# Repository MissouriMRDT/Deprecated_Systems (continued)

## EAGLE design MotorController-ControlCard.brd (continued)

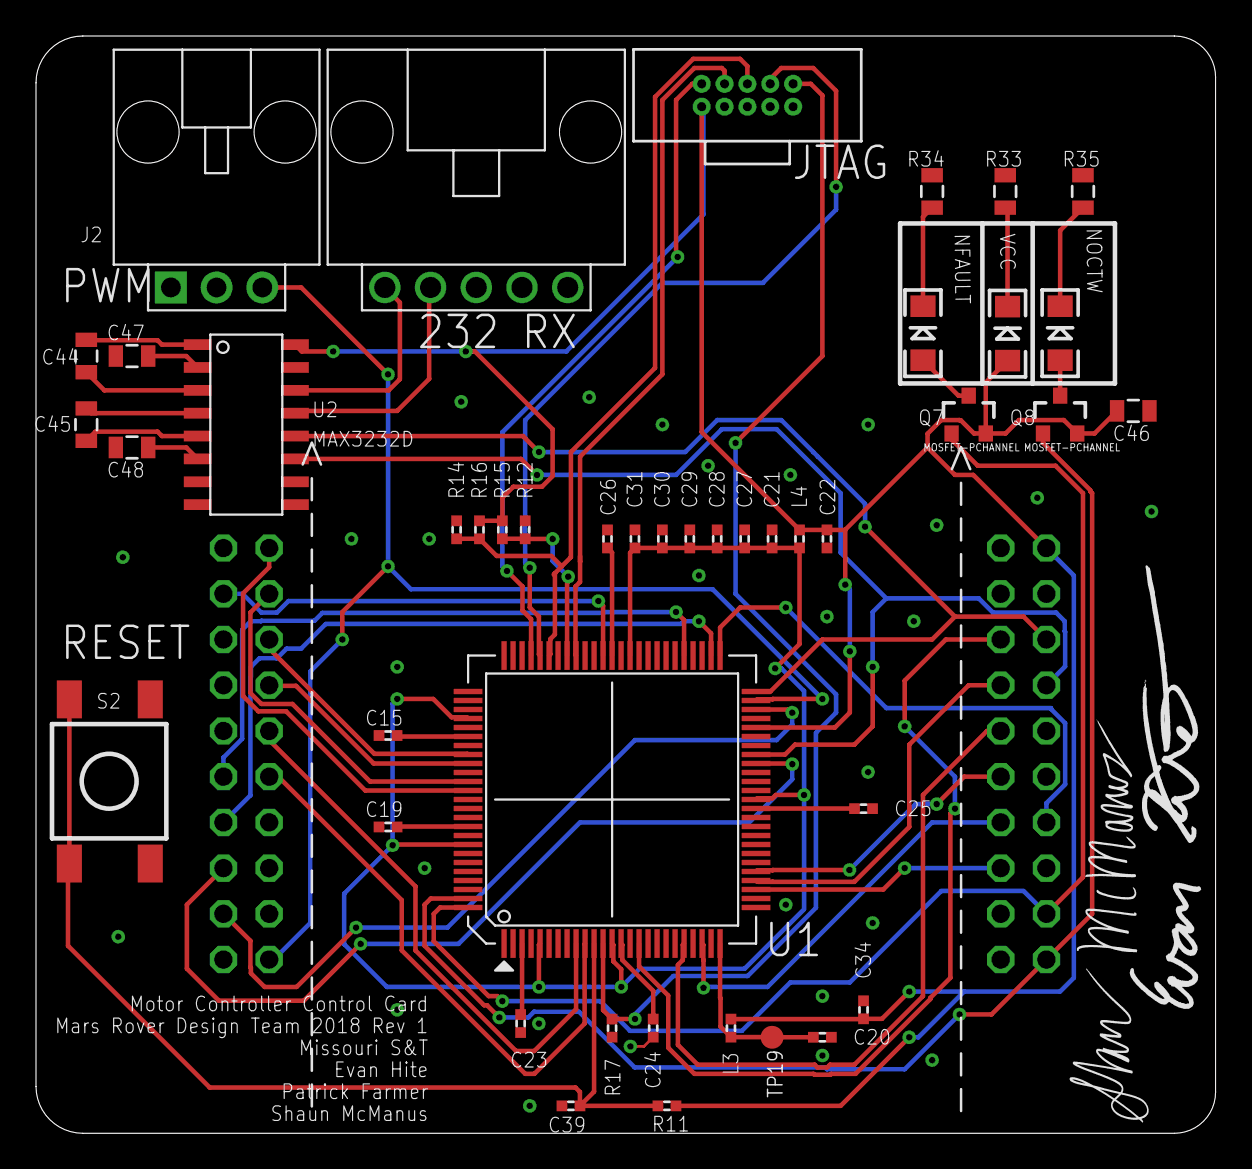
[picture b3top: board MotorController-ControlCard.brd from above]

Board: 2 copper layers, 65.5 x 61.0 mm, 47 parts (1 on the bottom side), 53 nets.

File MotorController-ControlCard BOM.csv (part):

Partlist exported from C:/Users/shotp/Documents/GitHub/MotorController-ControlCard/MotorController-ControlCard.sch at 1/24/2018 7:32 PM

Part Value                     Device                    Package                        Description                      OPERATING_VOLTAGE ORIENT PARTNO     PROD_ID     TP_SIGNAL_NAME
"C15  2.2u                      C-USC0402                 C0402                          CAPACITOR, American symbol                                                                     "
"C19  2.2u                      C-USC0402                 C0402                          CAPACITOR, American symbol                                                                     "
"C20  2.2u                      C-USC0402                 C0402                          CAPACITOR, American symbol                                                                     "
"C21  2.2u                      C-USC0402                 C0402                          CAPACITOR, American symbol                                                                     "
"C22  2.2u                      C-USC0402                 C0402                          CAPACITOR, American symbol                                                                     "
"C23  2.2u                      C-USC0402                 C0402                          CAPACITOR, American symbol                                                                     "
"C24  2.2u                      C-USC0402                 C0402                          CAPACITOR, American symbol                                                                     "
"C25  2.2u                      C-USC0402                 C0402                          CAPACITOR, American symbol                                                                     "
"C26  2.2u                      C-USC0402                 C0402                          CAPACITOR, American symbol                                                                     "
"C27  2.2u                      C-USC0402                 C0402                          CAPACITOR, American symbol                                                                     "
"C28  2.2u                      C-USC0402                 C0402                          CAPACITOR, American symbol                                                                     "
"C29  2.2u                      C-USC0402                 C0402                          CAPACITOR, American symbol                                                                     "
"C30  2.2u                      C-USC0402                 C0402                          CAPACITOR, American symbol                                                                     "
"C31  2.2u                      C-USC0402                 C0402                          CAPACITOR, American symbol                                                                     "
"C34  0.1u                      C-USC0402                 C0402                          CAPACITOR, American symbol                                                                     "
"C39  0.1u                      C-USC0402                 C0402                          CAPACITOR, American symbol                                                                     "
C44  0.1u                      CAP0805                   0805                           Capacitor                                                                                      
C45  0.1u                      CAP0805                   0805                           Capacitor                                                                                      
C46  0.1u                      CAP0805                   0805                           Capacitor                                                                                      
C47  0.1u                      CAP0805                   0805                           Capacitor                                                                                      
C48  0.1u                      CAP0805                   0805                           Capacitor                                                                                      
D7                             LED1206                   LED-1206                       LEDs                                                                                           
D8                             LED1206                   LED-1206                       LEDs                                                                                           
D9                             LED1206                   LED-1206                       LEDs                                                                                           
J2   SL03THROUGH_HOLE          SL03THROUGH_HOLE          MOLEX_SL_03_TH                 Molex 3-pin SL connector                           HORIZ  0705550002                           
"L3   BKP1005HS221-T            L-US0402                  R0402                          INDUCTOR, American symbol                                                                      "
"L4   BLM15PD600SN1D            L-US0402                  R0402                          INDUCTOR, American symbol                                                                      "
Q7   MOSFET-PCHANNEL           MOSFET-PCHANNEL           SOT23-3                        Generic PMOSFET                                                      TRANS-08285               
Q8   MOSFET-PCHANNEL           MOSFET-PCHANNEL           SOT23-3                        Generic PMOSFET                                                      TRANS-08285               
"R11  2.2k                      R-US_R0402                R0402                          RESISTOR, American symbol                                                                      "
"R12  2.2k                      R-US_R0402                R0402                          RESISTOR, American symbol                                                                      "
"R14  2.2k                      R-US_R0402                R0402                          RESISTOR, American symbol                                                                      "
"R15  820                       R-US_R0402                R0402                          RESISTOR, American symbol                                                                      "
"R16  820                       R-US_R0402                R0402                          RESISTOR, American symbol                                                                      "
"R17  2.2k                      R-US_R0402                R0402                          RESISTOR, American symbol                                                                      "
R33  330                       RESISTOR0805-RES          0805                           Resistor                                                                                       
R34  330                       RESISTOR0805-RES          0805                           Resistor                                                                                       
R35  330                       RESISTOR0805-RES          0805                           Resistor                                                                                       
S2   TP-1138K9-BE1125          FSMJSMA                   FSMJSMA                                                                                                                       
"TP19 TESTPAD_TPB1,27           TESTPAD_TPB1,27           TESTPAD_B1,27                  Test pad                                                                                       "
U$1  TIVA-123                  TIVA-123                  TIVA-C                         TIVA-C DEV BOARD (NON-CONNECTED)                                                               
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
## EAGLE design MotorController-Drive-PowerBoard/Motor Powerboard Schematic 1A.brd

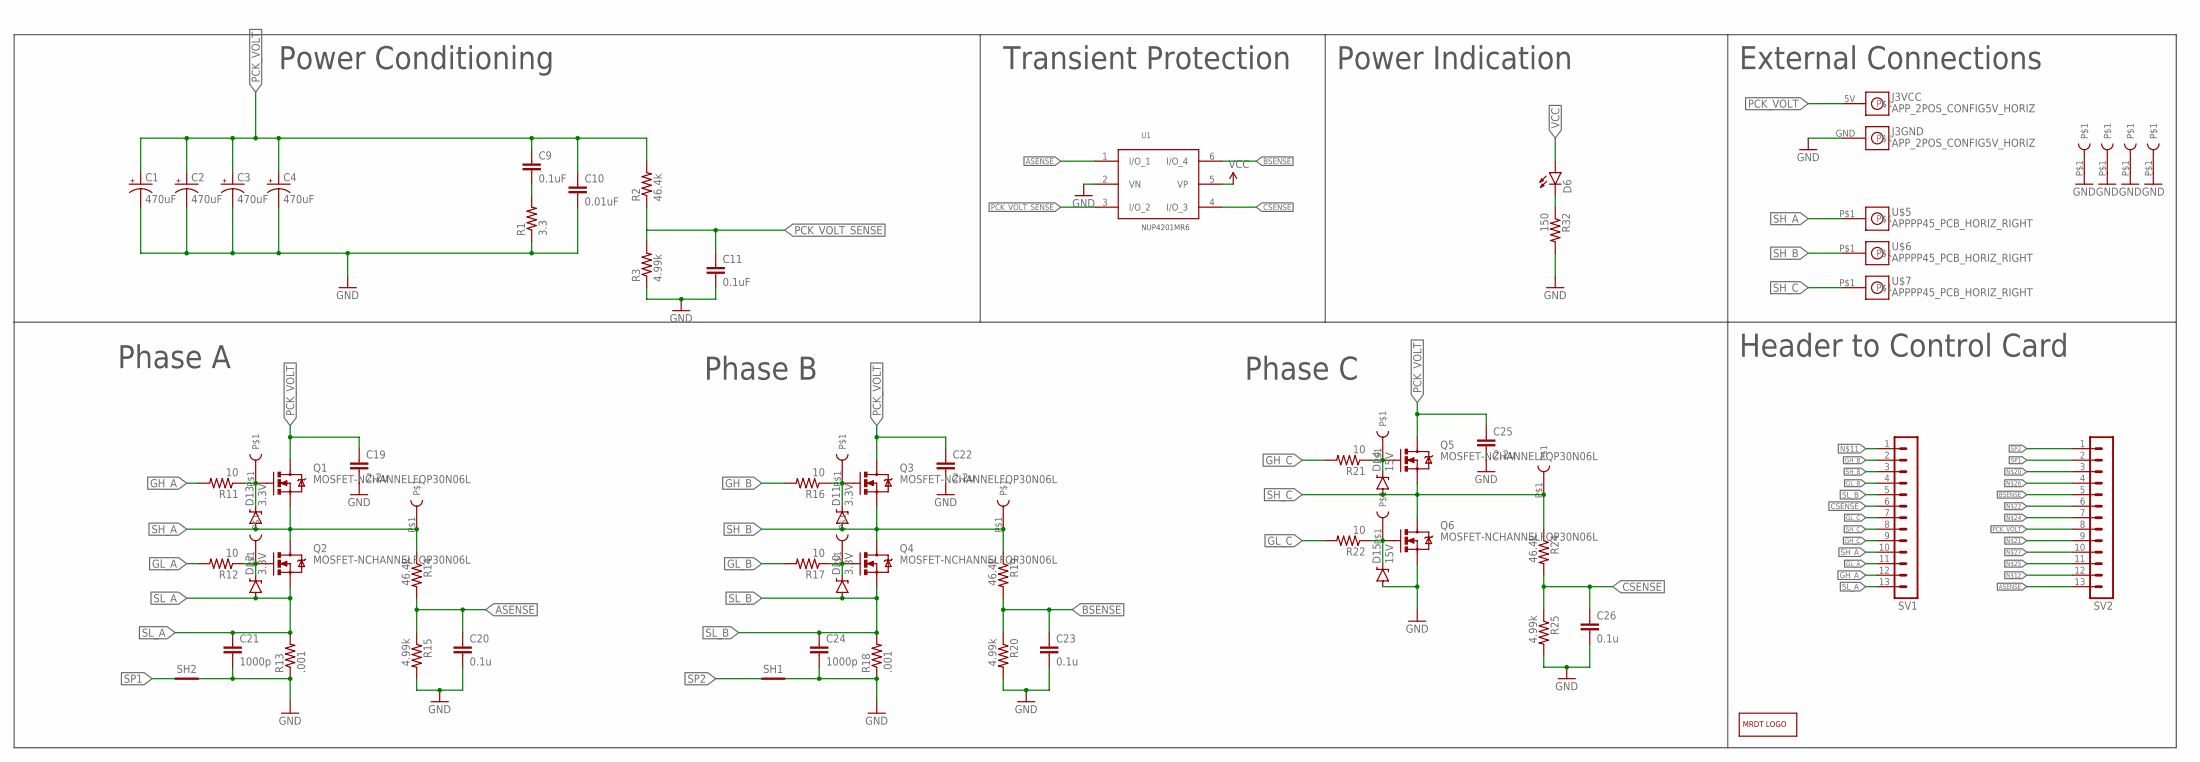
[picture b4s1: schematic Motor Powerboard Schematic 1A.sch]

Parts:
C1, C2, C3, C4: 470uF; CPOL-RADIAL-1000UF-25V
C9, C11: 0.1uF; 0805
C10: 0.01uF; 0805
C19, C22, C25: 2.2u; 1206
C20, C23, C26: 0.1u; 0805
C21, C24: 1000p; 0805
D6: LED1206; LED-1206
D10, D11, D12, D13: 3.3V; SOD-323
D14, D15: 15V; SOD-323
J3: APP_2POS_CONFIG5V_HORIZ; APP45_5V_HORIZ_CONFIG
LOGO1: MRDT_LOGO
Q1, Q2, Q3, Q4, Q5, Q6: MOSFET-NCHANNELFQP30N06L; TO220V
R1: 3.3; 1206
R2, R14, R19, R24: 46.4k; 0805
R3, R15, R20, R25: 4.99k; 0805
R11, R12, R16, R17, R21, R22: 10; 0805
R13, R18: .001; 1206
R32: 150; 0805
SH1, SH2: SHORT-HT5; SHORT_TOP-50
SV1, SV2: MA13-1
U1: NUP4201MR6; TSOP-6
U$5, U$6, U$7: APPPP45_PCB_HORIZ_RIGHT; APP45_PCB_HORIZ_RIGHT
U$12, U$15, U$16, U$17, U$18, U$19, U$20, U$24, U$25, U$26, U$27, U$28, U$29: TEST_POINT_0.1INDIAM

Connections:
ASENSE: C20.1, R14.2, R15.1, SV2.13, U1.1 (I/O_1)
BSENSE: C23.1, R19.2, R20.1, SV2.5, U1.6 (I/O_4)
CSENSE: C26.1, R24.2, R25.1, SV1.6, U1.4 (I/O_3)
GH_A: R11.2, SV1.12
GH_B: R16.2, SV1.2
GH_C: R21.2, SV1.9
GL_A: R12.2, SV1.11
GL_B: R17.2, SV1.4
GL_C: R22.2, SV1.7
GND: C1.2 (-), C2.2 (-), C3.2 (-), C4.2 (-), C10.2, C11.2, C19.2, C20.2, C21.2, C22.2, C23.2, C24.2, C25.2, C26.2, D15.A, J3.GND, Q6.3 (S), R1.1, R3.1, R13.1, R15.2, R18.1, R20.2, R25.2, R32.2, SH1.2, SH2.2, U1.2 (VN), U$26.P$1, U$27.P$1, U$28.P$1, U$29.P$1
unnamed: C9.2, R1.2
unnamed: D13.C, Q1.1 (G), R11.1, U$12.P$1
unnamed: D11.C, Q3.1 (G), R16.1, U$16.P$1
unnamed: D10.C, Q4.1 (G), R17.1, U$17.P$1
unnamed: D12.C, Q2.1 (G), R12.1, U$15.P$1
unnamed: D14.C, Q5.1 (G), R21.1, U$18.P$1
unnamed: D15.C, Q6.1 (G), R22.1, U$19.P$1
unnamed: D6.C, R32.1
PCK_VOLT: C1.1 (+), C2.1 (+), C3.1 (+), C4.1 (+), C9.1, C10.1, C19.1, C22.1, C25.1, J3.5V, Q1.2 (D), Q3.2 (D), Q5.2 (D), R2.2, SV2.8
PCK_VOLT_SENSE: C11.1, R2.1, R3.2, U1.3 (I/O_2)
SH_A: D13.A, Q1.3 (S), Q2.2 (D), R14.1, SV1.10, U$5.P$1, U$25.P$1
SH_B: D11.A, Q3.3 (S), Q4.2 (D), R19.1, SV1.3, U$6.P$1, U$24.P$1
SH_C: D14.A, Q5.3 (S), Q6.2 (D), R24.1, SV1.8, U$7.P$1, U$20.P$1
SL_A: C21.1, D12.A, Q2.3 (S), R13.2, SV1.13
SL_B: C24.1, D10.A, Q4.3 (S), R18.2, SV1.5
SP1: SH2.1, SV2.2
SP2: SH1.1, SV2.1
VCC: D6.A, U1.5 (VP)

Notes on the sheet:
Transient Protection
Phase A
Phase B
Phase C
External Connections
Power Indication
Power Conditioning
Header to Control Card

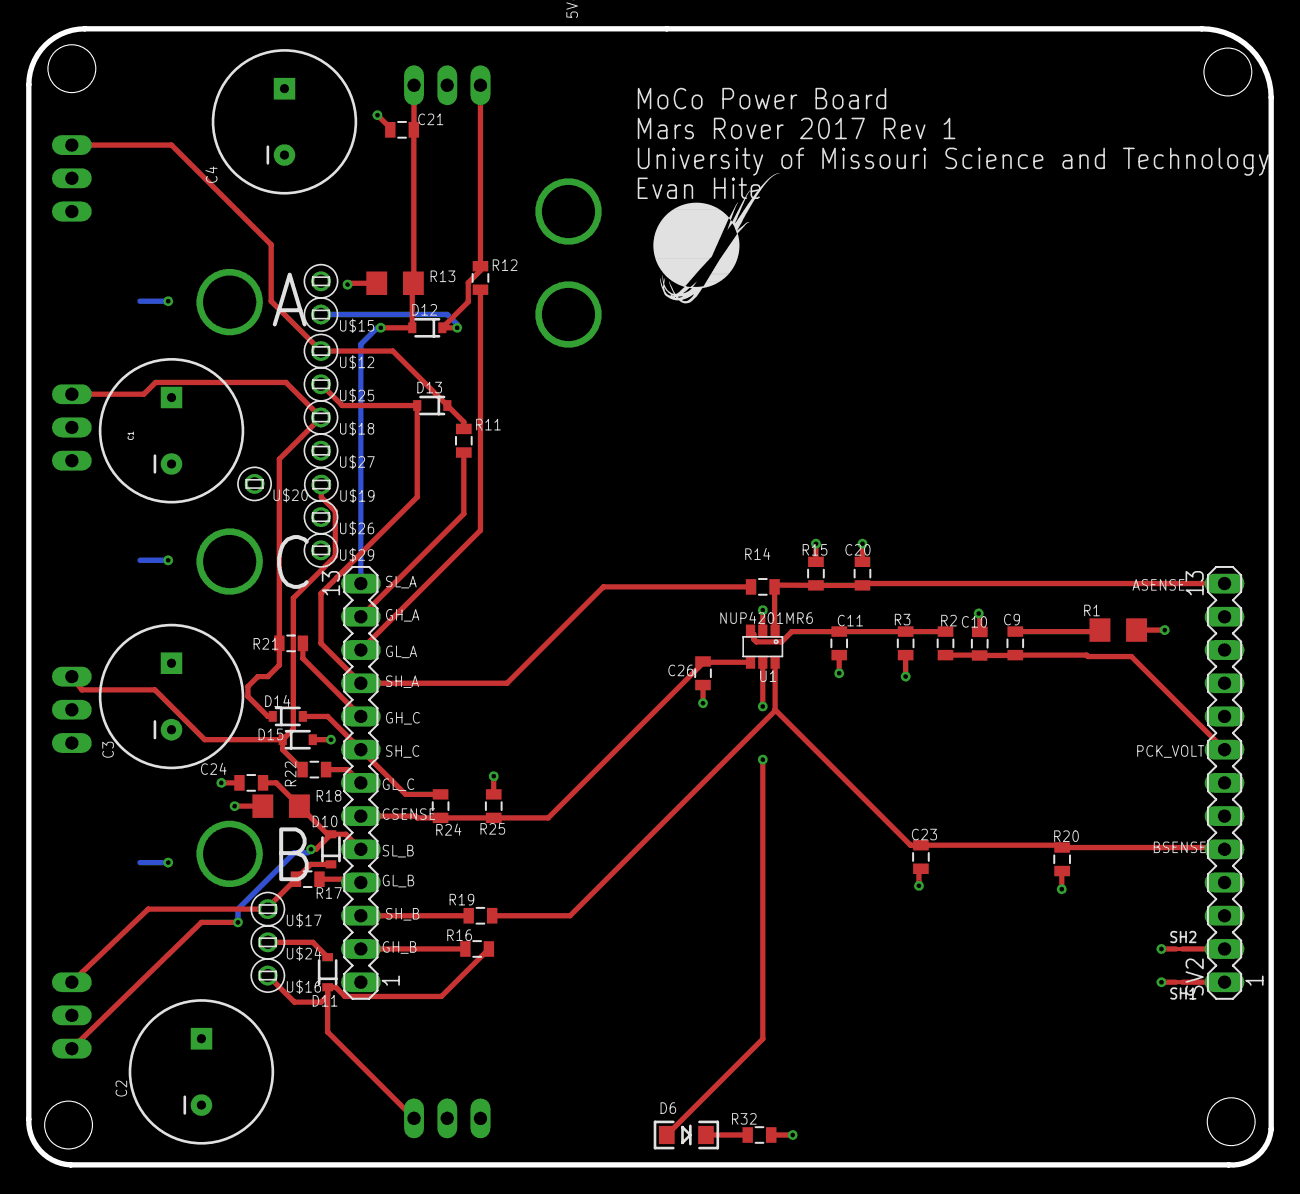
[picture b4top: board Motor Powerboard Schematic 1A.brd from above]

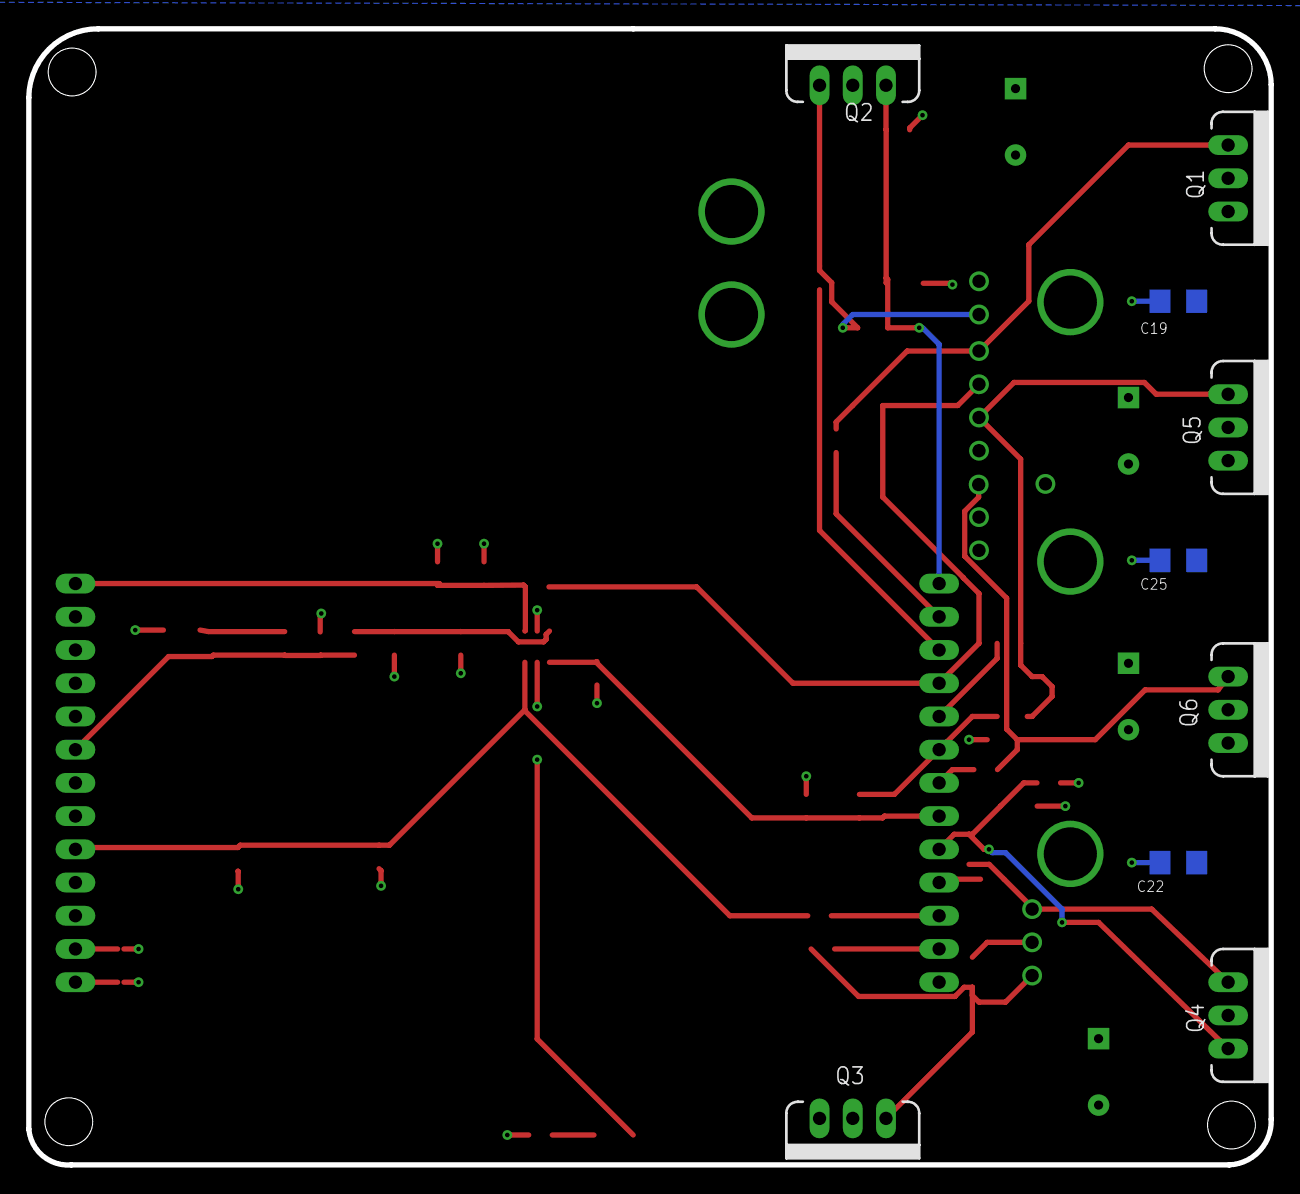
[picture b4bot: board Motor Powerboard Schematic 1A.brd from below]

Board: 4 copper layers, 95.0 x 86.9 mm, 69 parts (9 on the bottom side), 28 nets.

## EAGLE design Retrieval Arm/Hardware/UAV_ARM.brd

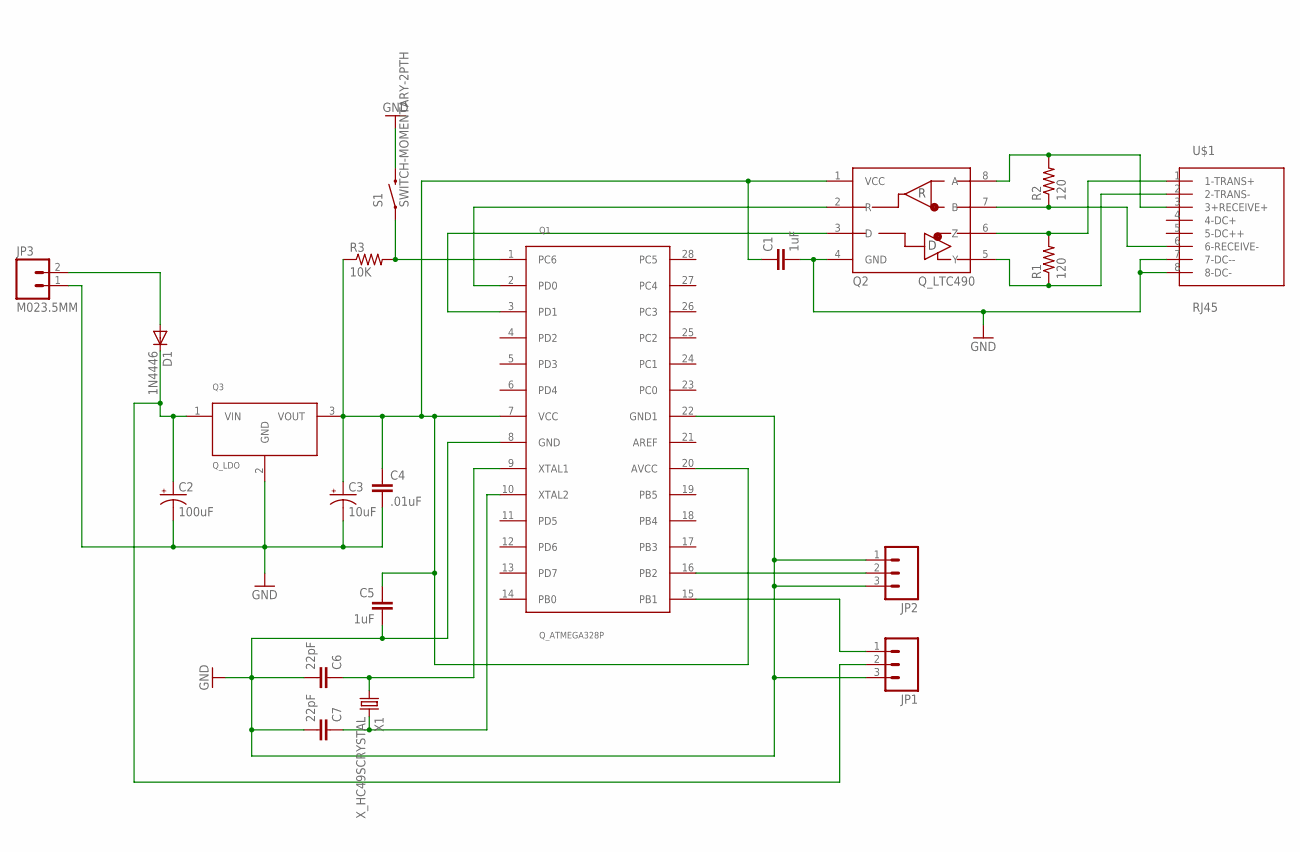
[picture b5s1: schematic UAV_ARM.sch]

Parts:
C1, C5: 1uF; CAP-PTH-SMALL-KIT
C2: 100uF; CPOL-RADIAL-100UF-25V
C3: 10uF; CPOL-RADIAL-10UF-25V
C4: .01uF; CAP-PTH-SMALL-KIT
C6, C7: 22pF; CAP-PTH-SMALL-KIT
D1: 1N4446; DO35-10
JP1, JP2: M03POLAR; MOLEX-1X3
JP3: M023.5MM; SCREWTERMINAL-3.5MM-2
Q1: Q_ATMEGA328P; DIP28
Q2: Q_LTC490; DIP8
Q3: Q_LDO; TO-220
R1, R2: 120; 0204/7
R3: 10K; 0204/7
S1: SWITCH-MOMENTARY-2PTH; TACTILE-PTH
U$1: RJ45; RJ45-CAT5E
X1: X_HC49SCRYSTAL; HC-49

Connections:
GND: C1.2, C2.2 (-), C3.2 (-), C4.2, C5.2, C6.2, C7.2, JP1.3, JP2.1, JP2.3, JP3.1, Q1.8 (GND), Q1.22 (GND1), Q2.4 (GND), Q3.2 (GND), S1.3 (2), U$1.7 (7-DC--), U$1.8 (8-DC-)
unnamed: Q2.8 (A), R2.2, U$1.3 (3+RECEIVE+)
unnamed: Q2.7 (B), R2.1, U$1.6 (6-RECEIVE-)
unnamed: Q2.5 (Y), R1.1, U$1.2 (2-TRANS-)
unnamed: Q2.6 (Z), R1.2, U$1.1 (1-TRANS+)
unnamed: C2.1 (+), D1.C, JP1.2, Q3.1 (VIN)
unnamed: C1.1, C3.1 (+), C4.1, C5.1, Q1.7 (VCC), Q1.20 (AVCC), Q2.1 (VCC), Q3.3 (VOUT), R3.1
unnamed: Q1.3 (PD1), Q2.3 (D)
unnamed: Q1.2 (PD0), Q2.2 (R)
unnamed: Q1.1 (PC6), R3.2, S1.1
unnamed: C6.1, Q1.9 (XTAL1), X1.P$1 (1)
unnamed: C7.1, Q1.10 (XTAL2), X1.P$2 (2)
unnamed: JP2.2, Q1.16 (PB2)
unnamed: JP1.1, Q1.15 (PB1)
unnamed: D1.A, JP3.2

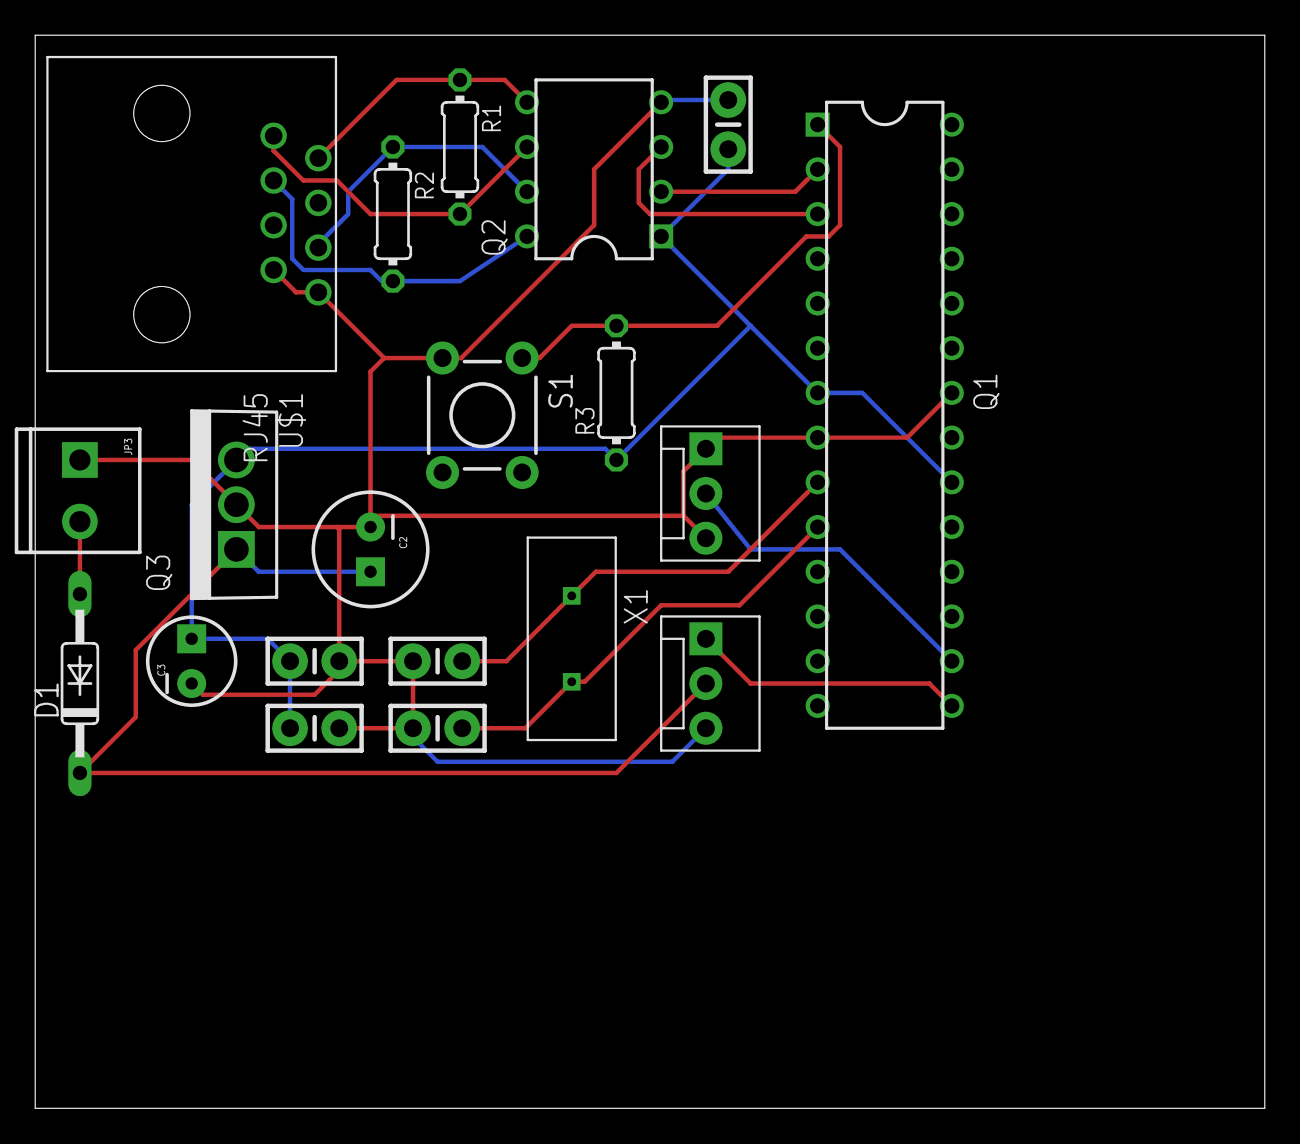
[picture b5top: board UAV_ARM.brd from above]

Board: 2 copper layers, 69.8 x 61.0 mm, 20 parts (0 on the bottom side), 15 nets.

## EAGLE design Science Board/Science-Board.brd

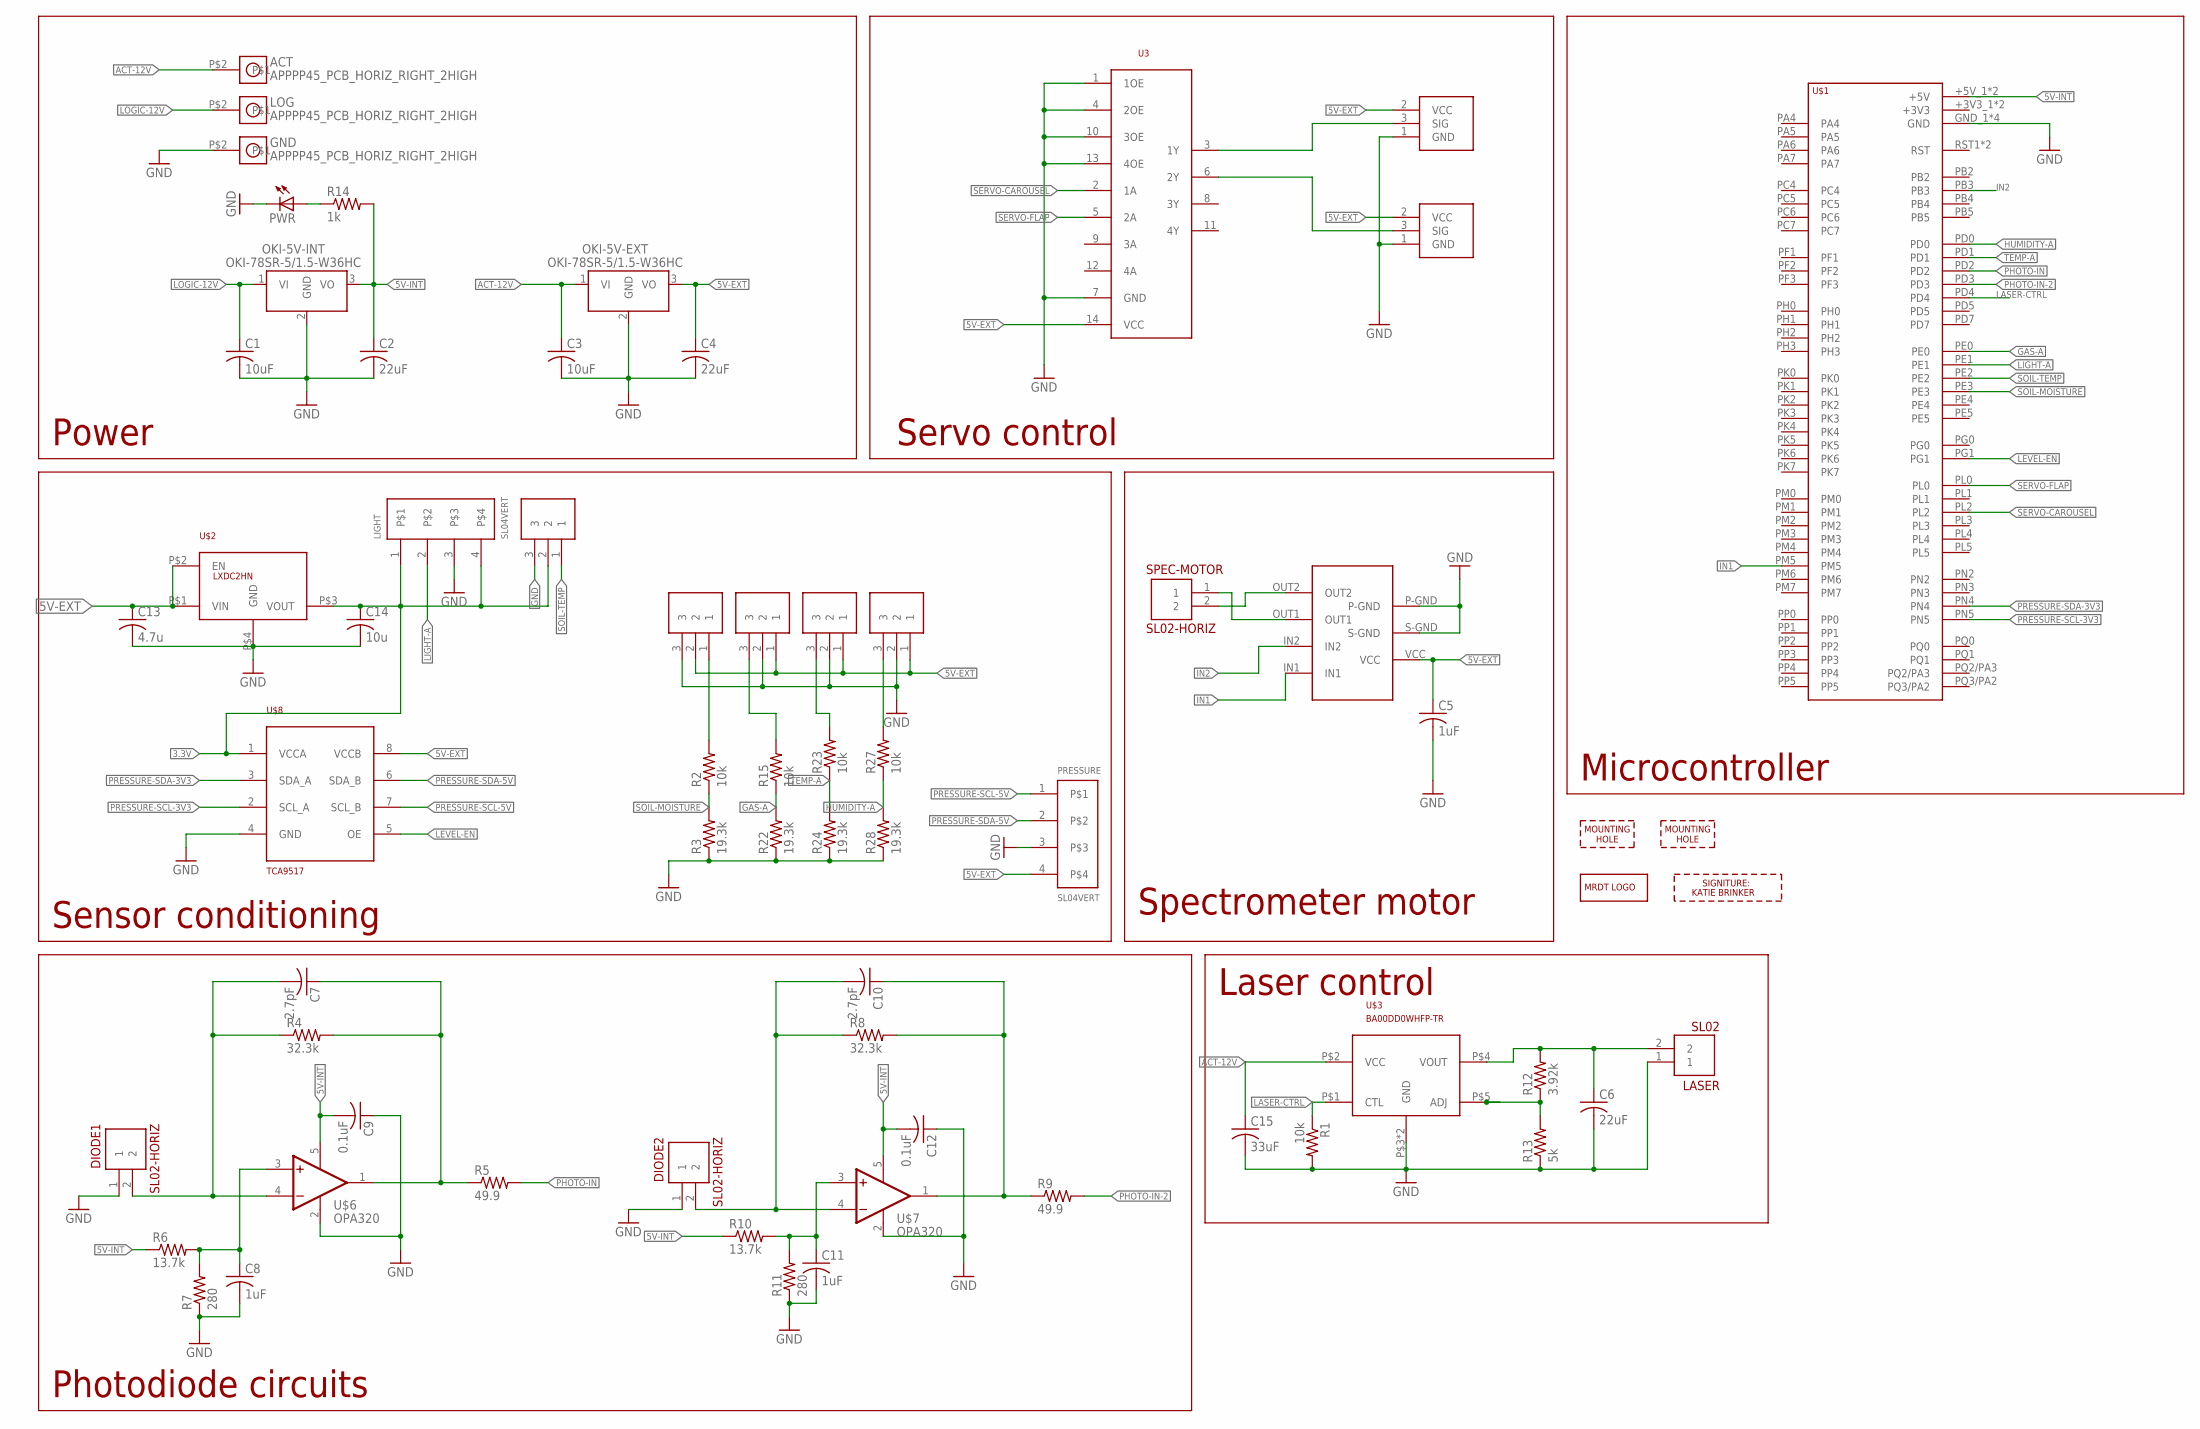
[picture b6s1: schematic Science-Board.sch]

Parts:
ACT: APPPP45_PCB_HORIZ_RIGHT_2HIGH; APP45_PCB_HORIZ_RIGHT_2HIGH
C1, C3: 10uF; C0805
C2, C4, C6: 22uF; C0805
C5, C8, C11: 1uF; C0805
C7, C10: 2.7pF; C0805
C9, C12: 0.1uF; C0805
C13: 4.7u; C0805
C14: 10u; C0805
C15: 33uF; C0805
CAROUSEL: SERVOMOLEX_SL_THRU_HOLE; MOLEX_SL_03_TH
DIODE1, DIODE2: SL02-HORIZ; MOLEX-70551-0001
FLAP: SERVOMOLEX_SL_THRU_HOLE; MOLEX_SL_03_TH
GAS: SL03; MOLEX-70543-0002
GND: APPPP45_PCB_HORIZ_RIGHT_2HIGH; APP45_PCB_HORIZ_RIGHT_2HIGH
H3, H4: MOUNTING_HOLE#6; #6_SCREW
HUMID: SL03; MOLEX-70543-0002
LASER: SL02; MOLEX-70543-0001
LIGHT: SL04VERT; MOLEX-70543-0003
LOG: APPPP45_PCB_HORIZ_RIGHT_2HIGH; APP45_PCB_HORIZ_RIGHT_2HIGH
LOGO1: MRDT_LOGO
OKI-5V-EXT, OKI-5V-INT: OKI-78SR-5/1.5-W36HC; OKI-78SR_HORIZ
PRESSURE: SL04VERT; MOLEX-70543-0003
PWR: LEDCHIP-LED0805; CHIP-LED0805
R1: 10k; M0805
R2, R15, R23, R27: 10k; R0805
R3, R22, R24, R28: 19.3k; R0805
R4, R8: 32.3k; M0805
R5, R9: 49.9; M0805
R6, R10: 13.7k; M0805
R7, R11: 280; M0805
R12: 3.92k; M0805
R13: 5k; M0805
R14: 1k; M0805
SOIL-MOIST: SL03; MOLEX-70543-0002
SOIL-TEMP: SL03; MOLEX-70543-0002
SPEC-MOTOR: SL02-HORIZ; MOLEX-70551-0001
TEMP: SL03; MOLEX-70543-0002
U3: SN74AHCT125; SOIC14
U$1: TIVA-1294; TIVA-C-CONNECTED
U$2: LXDC2HN; 4-SMD
U$3: BA00DD0WHFP-TR; TO-263-6
U$4: KATIE-BRINKER; KATIE-BRINKER-SIG
U$6, U$7: OPA320; SOT-23-5
U$8: TCA9517; SOIC8
U$10: LB1930MC; SOIC10

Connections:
3.3V: C14.1, LIGHT.1, LIGHT.4, SOIL-TEMP.2, U$2.P$3 (VOUT), U$8.1 (VCCA)
5V-EXT: C4.1, C5.1, C13.1, CAROUSEL.2 (VCC), FLAP.2 (VCC), GAS.1, HUMID.1, OKI-5V-EXT.3 (VO), PRESSURE.4, SOIL-MOIST.2, TEMP.1, U3.14 (VCC), U$2.P$1 (VIN), U$2.P$2 (EN), U$8.8 (VCCB), U$10.VCC
5V-INT: C2.1, C9.2, C12.2, OKI-5V-INT.3 (VO), R6.1, R10.1, R14.2, U$1.+5V_1 (+5V), U$1.+5V_2 (+5V), U$6.5 (OFF1), U$7.5 (OFF1)
ACT-12V: ACT.P$2, C3.1, C15.1, OKI-5V-EXT.1 (VI), U$3.P$2 (VCC)
GAS-A: R15.1, R22.2, U$1.PE0
GND: C1.2, C2.2, C3.2, C4.2, C5.2, C6.2, C8.2, C9.1, C11.2, C12.1, C13.2, C14.2, C15.2, CAROUSEL.1 (GND), DIODE1.1, DIODE2.1, FLAP.1 (GND), GAS.2, GND.P$2, HUMID.2, LASER.1, LIGHT.3, OKI-5V-EXT.2 (GND), OKI-5V-INT.2 (GND), PRESSURE.3, PWR.C, R1.2, R3.1, R7.1, R11.1, R13.1, R22.1, R24.1, R28.1, SOIL-MOIST.3, SOIL-TEMP.3, TEMP.2, U3.1 (1OE), U3.4 (2OE), U3.7 (GND), U3.10 (3OE), U3.13 (4OE), U$1.GND_1 (GND), U$1.GND_2 (GND), U$1.GND_3 (GND), U$1.GND_4 (GND), U$2.P$4 (GND), U$3.P$3 (GND), U$3.P$6 (GND), U$6.2 (OFF2), U$7.2 (OFF2), U$8.4 (GND), U$10.P-GND, U$10.S-GND
HUMIDITY-A: R27.1, R28.2, U$1.PD0
IN1: U$1.PM5, U$10.IN1
IN2: U$1.PB3, U$10.IN2
LASER-CTRL: R1.1, U$1.PD4, U$3.P$1 (CTL)
LEVEL-EN: U$1.PG1, U$8.5 (OE)
LIGHT-A: LIGHT.2, U$1.PE1
LOGIC-12V: C1.1, LOG.P$2, OKI-5V-INT.1 (VI)
unnamed: SPEC-MOTOR.2, U$10.OUT2
unnamed: SPEC-MOTOR.1, U$10.OUT1
unnamed: C6.1, LASER.2, R12.2, U$3.P$4 (VOUT)
unnamed: C7.2, DIODE1.2, R4.1, U$6.4 (-IN)
unnamed: R2.2, SOIL-MOIST.1
unnamed: R23.2, TEMP.3
unnamed: C7.1, R4.2, R5.1, U$6.1 (OUT)
unnamed: C10.2, DIODE2.2, R8.1, U$7.4 (-IN)
unnamed: C8.1, R6.2, R7.2, U$6.3 (+IN)
unnamed: CAROUSEL.3 (SIG), U3.3 (1Y)
unnamed: FLAP.3 (SIG), U3.6 (2Y)
unnamed: C10.1, R8.2, R9.1, U$7.1 (OUT)
unnamed: C11.1, R10.2, R11.2, U$7.3 (+IN)
unnamed: PWR.A, R14.1
unnamed: GAS.3, R15.2
unnamed: HUMID.3, R27.2
unnamed: R12.1, R13.2, U$3.P$5 (ADJ)
PHOTO-IN: R5.2, U$1.PD2
PHOTO-IN-2: R9.2, U$1.PD3
PRESSURE-SCL-3V3: U$1.PN5, U$8.2 (SCL_A)
PRESSURE-SCL-5V: PRESSURE.1, U$8.7 (SCL_B)
PRESSURE-SDA-3V3: U$1.PN4, U$8.3 (SDA_A)
PRESSURE-SDA-5V: PRESSURE.2, U$8.6 (SDA_B)
SERVO-CAROUSEL: U3.2 (1A), U$1.PL2
SERVO-FLAP: U3.5 (2A), U$1.PL0
SOIL-MOISTURE: R2.1, R3.2, U$1.PE3
SOIL-TEMP: SOIL-TEMP.1, U$1.PE2
TEMP-A: R23.1, R24.2, U$1.PD1

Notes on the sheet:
Microcontroller
Spectrometer motor
Photodiode circuits
Laser control
Servo control
Sensor conditioning
Power

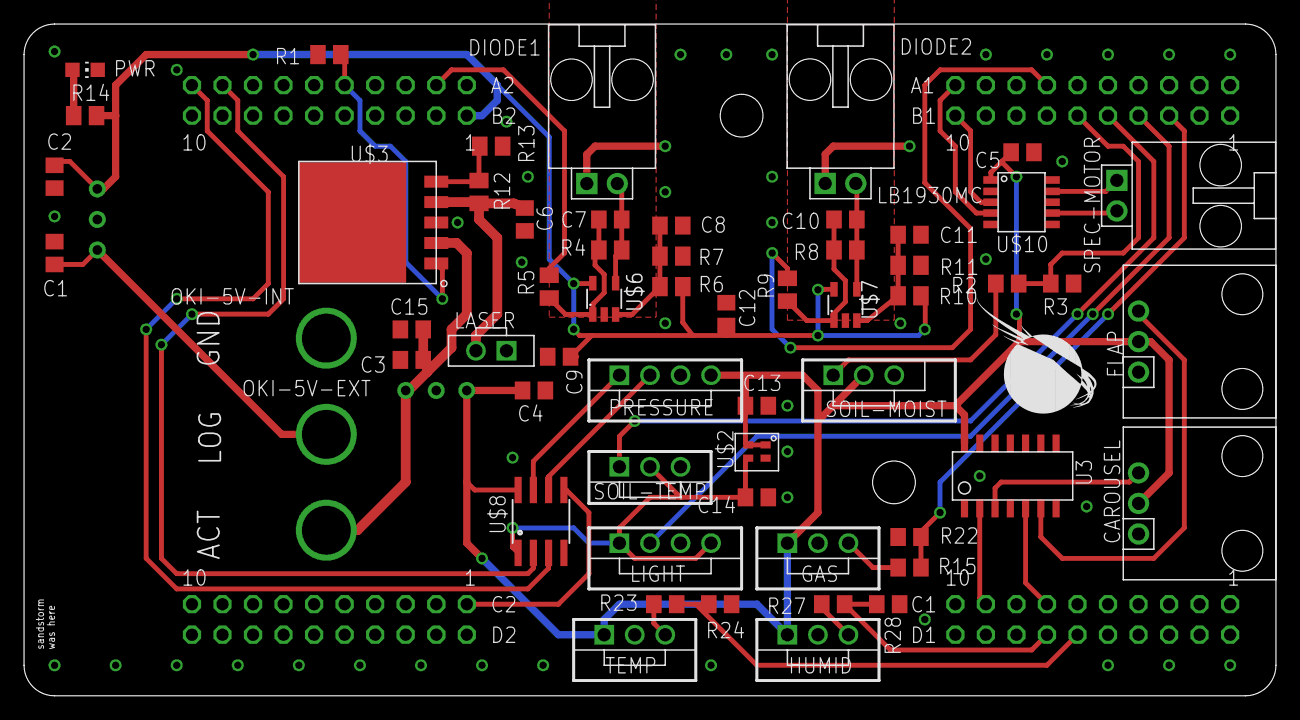
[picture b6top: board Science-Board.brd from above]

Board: 2 copper layers, 104.1 x 55.9 mm, 66 parts (1 on the bottom side), 41 nets.
